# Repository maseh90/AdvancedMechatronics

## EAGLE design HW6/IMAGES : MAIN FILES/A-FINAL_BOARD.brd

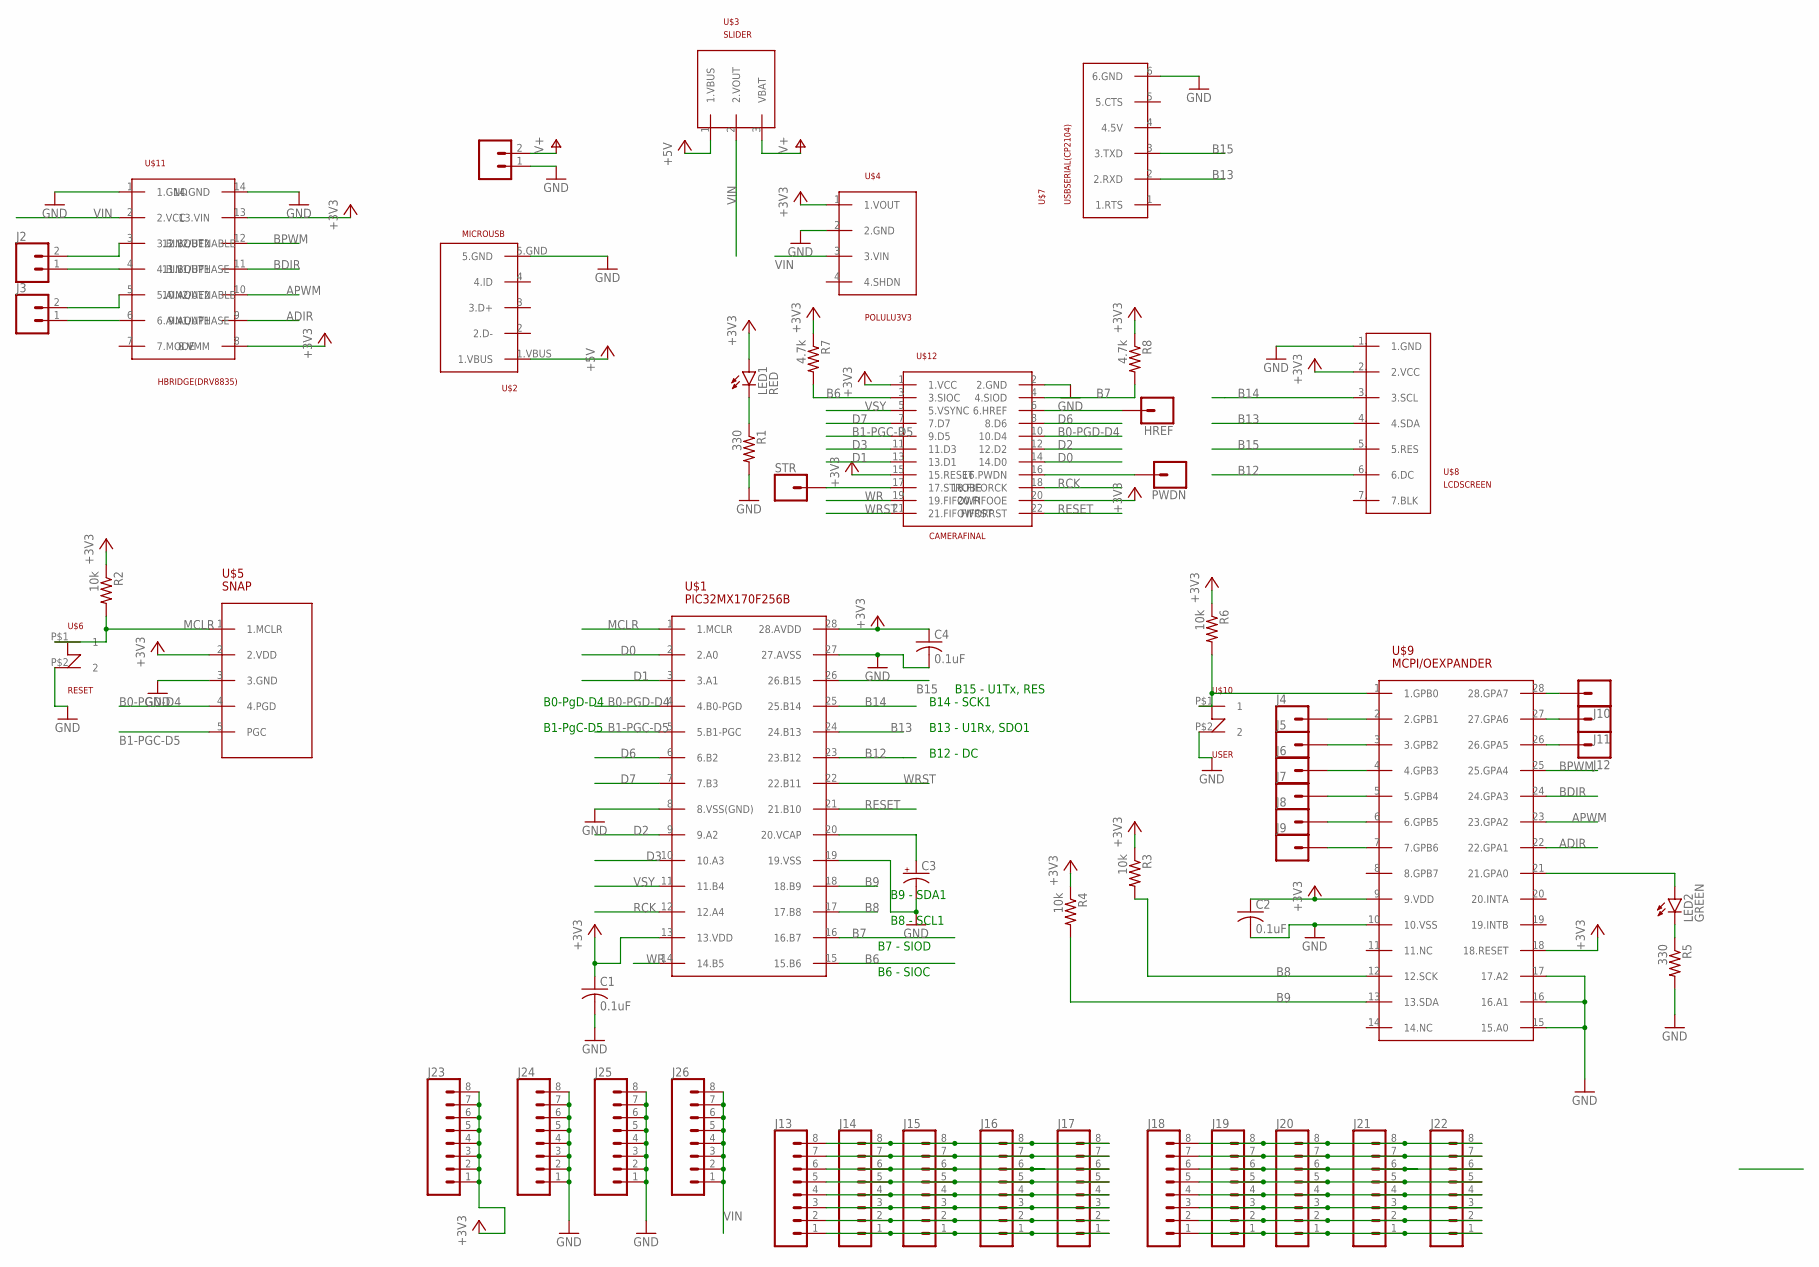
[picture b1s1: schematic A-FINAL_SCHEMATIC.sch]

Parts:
C1, C2, C4: 0.1uF; C025-030X050
C3: CPOL-USB45181B; B45181B
HREF: CONN_01; 1X01
J1: CONN_02-JST-2-PTH-NO_SILK; JST-2-PTH-NS
J2, J3: CONN_02; 1X02
J4, J5, J6, J7, J8, J9, J10, J11, J12: CONN_01; 1X01
J13, J14, J15, J16, J17, J18, J19, J20, J21, J22, J23, J24, J25, J26: CONN_08"; 1X08
LED1: RED; LED3MM
LED2: GREEN; LED3MM
PWDN: CONN_01; 1X01
R1, R5: 330; 0207/10
R2, R3, R4, R6: 10k; 0207/10
R7, R8: 4.7k; 0207/10
STR: CONN_01; 1X01
U$1: PIC32MX170F256B; DIL28-3
U$2: MICROUSB
U$3: SLIDER; SLIDE
U$4: POLULU3V3
U$5: SNAP; 1X05
U$6: RESET; PUSH
U$7: USBSERIAL(CP2104)
U$8: LCDSCREEN
U$9: MCPI/OEXPANDER
U$10: USER; PUSH
U$11: HBRIDGE(DRV8835)
U$12: CAMERAFINAL; CAMERA_FINAL

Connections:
+3V3: C1.1, C2.1, C4.1, J23.1, J23.2, J23.3, J23.4, J23.5, J23.6, J23.7, J23.8, LED1.A, R2.1, R3.1, R4.1, R6.1, R7.1, R8.1, U$1.13 (13.VDD), U$1.28 (28.AVDD), U$4.1 (1.VOUT), U$5.2 (2.VDD), U$8.2. (2.VCC), U$9.9 (9.VDD), U$9.18 (18.RESET), U$11.8 (8.VMM), U$11.13 (13.VIN), U$12.1 (1.VCC), U$12.15 (15.RESET), U$12.20 (20.FIFOOE)
+5V: U$2.1.VBUS, U$3.1 (1.VBUS)
ADIR: U$9.22 (22.GPA1), U$11.9 (9.AOUT1)
APWM: U$9.23 (23.GPA2), U$11.10 (10.AOUT2)
B0-PGD-D4: U$1.4 (4.B0-PGD), U$5.4 (4.PGD), U$12.10 (10.D4)
B1-PGC-D5: U$1.5 (5.B1-PGC), U$5.5 (PGC), U$12.9 (9.D5)
B6: R7.2, U$1.15 (15.B6), U$12.3 (3.SIOC)
B7: R8.2, U$1.16 (16.B7), U$12.4 (4.SIOD)
B8: R3.2, U$1.17 (17.B8), U$9.12 (12.SCK)
B9: R4.2, U$1.18 (18.B9), U$9.13 (13.SDA)
B12: U$1.23 (23.B12), U$8.6. (6.DC)
B13: U$1.24 (24.B13), U$7.2 (2.RXD), U$8.4. (4.SDA)
B14: U$1.25 (25.B14), U$8.3. (3.SCL)
B15: U$1.26 (26.B15), U$7.3 (3.TXD), U$8.5. (5.RES)
BDIR: U$9.24 (24.GPA3), U$11.11 (11.BOUT1)
BPWM: U$9.25 (25.GPA4), U$11.12 (12.BOUT2)
D0: U$1.2 (2.A0), U$12.14 (14.D0)
D1: U$1.3 (3.A1), U$12.13 (13.D1)
D2: U$1.9 (9.A2), U$12.12 (12.D2)
D3: U$1.10 (10.A3), U$12.11 (11.D3)
D6: U$1.6 (6.B2), U$12.8 (8.D6)
D7: U$1.7 (7.B3), U$12.7 (7.D7)
GND: C1.2, C2.2, C3.-, C4.2, J1.1, J24.1, J24.2, J24.3, J24.4, J24.5, J24.6, J24.7, J24.8, J25.1, J25.2, J25.3, J25.4, J25.5, J25.6, J25.7, J25.8, R1.2, R5.2, U$1.8 (8.VSS(GND)), U$1.19 (19.VSS), U$1.27 (27.AVSS), U$2.5.GND, U$4.2 (2.GND), U$5.3 (3.GND), U$6.P$2 (2), U$7.6 (6.GND), U$8.1. (1.GND), U$9.10 (10.VSS), U$9.15 (15.A0), U$9.16 (16.A1), U$9.17 (17.A2), U$10.P$2 (2), U$11.1 (1.GND), U$11.14 (14.GND), U$12.2 (2.GND)
MCLR: R2.2, U$1.1 (1.MCLR), U$5.1 (1.MCLR), U$6.P$1 (1)
unnamed: LED1.K (C), R1.1
unnamed: LED2.A, U$9.21 (21.GPA0)
unnamed: C3.+, U$1.20 (20.VCAP)
unnamed: LED2.K (C), R5.1
unnamed: R6.2, U$9.1 (1.GPB0), U$10.P$1 (1)
unnamed: J2.2, U$11.3 (3.BIN2/BENABLE)
unnamed: J2.1, U$11.4 (4.BIN1/BPHASE)
unnamed: J3.2, U$11.5 (5.AIN2/AENABLE)
unnamed: J3.1, U$11.6 (6.AIN1/APHASE)
unnamed: HREF.1, U$12.6 (6.HREF)
unnamed: PWDN.1, U$12.16 (16.PWDN)
unnamed: STR.1, U$12.17 (17.STROBE)
unnamed: J4.1, U$9.2 (2.GPB1)
unnamed: J5.1, U$9.3 (3.GPB2)
unnamed: J6.1, U$9.4 (4.GPB3)
unnamed: J7.1, U$9.5 (5.GPB4)
unnamed: J8.1, U$9.6 (6.GPB5)
unnamed: J9.1, U$9.7 (7.GPB6)
unnamed: J10.1, U$9.28 (28.GPA7)
unnamed: J11.1, U$9.27 (27.GPA6)
unnamed: J12.1, U$9.26 (26.GPA5)
unnamed: J18.8, J19.8, J20.8, J21.8, J22.8
unnamed: J13.8, J14.8, J15.8, J16.8, J17.8
unnamed: J18.7, J19.7, J20.7, J21.7, J22.7
unnamed: J18.6, J19.6, J20.6, J21.6, J22.6
unnamed: J18.5, J19.5, J20.5, J21.5, J22.5
unnamed: J18.4, J19.4, J20.4, J21.4, J22.4
unnamed: J18.3, J19.3, J20.3, J21.3, J22.3
unnamed: J18.2, J19.2, J20.2, J21.2, J22.2
unnamed: J18.1, J19.1, J20.1, J21.1, J22.1
unnamed: J13.7, J14.7, J15.7, J16.7, J17.7
unnamed: J13.6, J14.6, J15.6, J16.6, J17.6
unnamed: J13.5, J14.5, J15.5, J16.5, J17.5
unnamed: J13.4, J14.4, J15.4, J16.4, J17.4
unnamed: J13.3, J14.3, J15.3, J16.3, J17.3
unnamed: J13.2, J14.2, J15.2, J16.2, J17.2
unnamed: J13.1, J14.1, J15.1, J16.1, J17.1
RCK: U$1.12 (12.A4), U$12.18 (18.FIFORCK)
RESET: U$1.21 (21.B10), U$12.22 (FIFORRST)
V+: J1.2, U$3.3 (VBAT)
VIN: J26.1, J26.2, J26.3, J26.4, J26.5, J26.6, J26.7, J26.8, U$3.2 (2.VOUT), U$4.3 (3.VIN), U$11.2 (2.VCC)
VSY: U$1.11 (11.B4), U$12.5 (5.VSYNC)
WR: U$1.14 (14.B5), U$12.19 (19.FIFOWR)
WRST: U$1.22 (22.B11), U$12.21 (21.FIFOWRST)

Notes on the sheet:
B15 - U1Tx, RES
B13 - U1Rx, SDO1
B14 - SCK1
B12 - DC
B9 - SDA1
B8 - SCL1
B7 - SIOD
B6 - SIOC
B0-PgD-D4
B1-PgC-D5

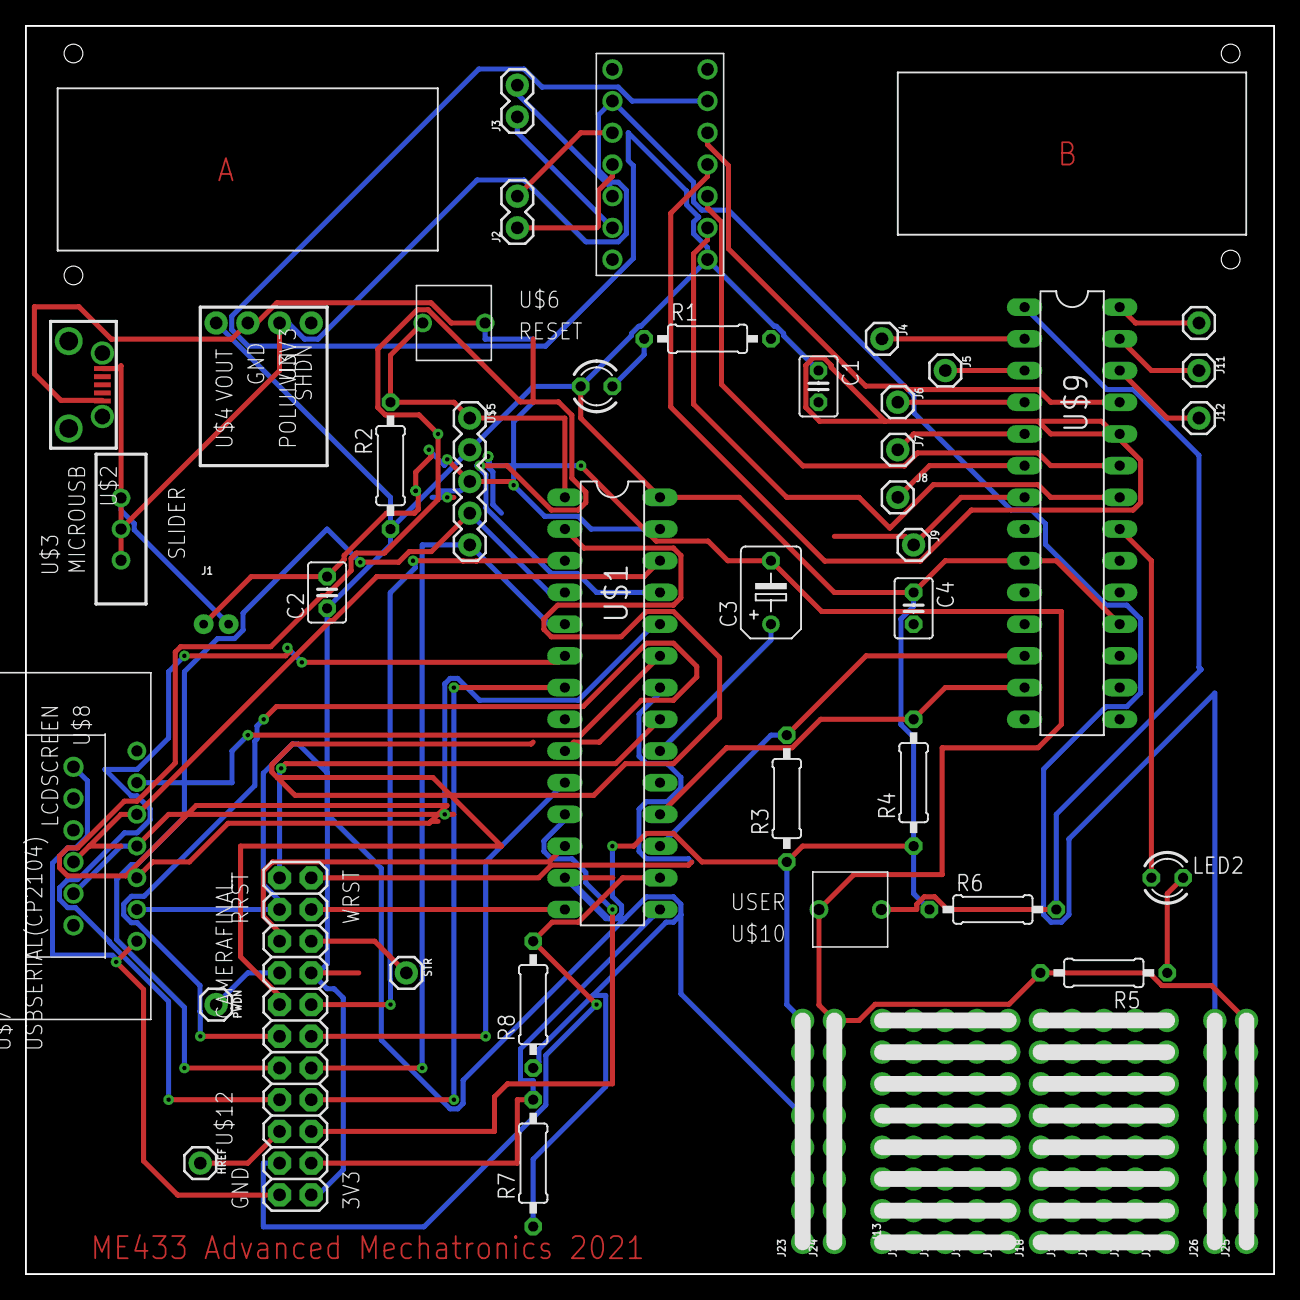
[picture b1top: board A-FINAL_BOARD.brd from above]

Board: 2 copper layers, 100.0 x 100.0 mm, 55 parts (0 on the bottom side), 68 nets.

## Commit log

2021-04-09 Uploaded HW2 Files
    This is my submission for HW2. I used a combination of the pre-provided reference code, the lecture video, online coding help guides (and StackOverflow), and documentation on choosing FIR filters. Th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
2021-04-17 Added HW3 (Lab Kit picture) folder
2021-04-18 Uploaded HW4 manually in browser
    I kept receiving "Unable to merge unrelated histories in this repository." errors, so I dragged/dropped the HW4 files here.
2021-04-18 Deleted HW4 directory
2021-04-18 Added HW4 files manually in browser
    I manually dragged/dropped the HW4 file here because I kept receiving "Unable to merge unrelated histories in this repository." messages after changing the original project name.
2021-04-18 Added Requested Images to HW4
2021-04-25 Added HW5 program files
2021-04-25 deleted for re-upload
2021-04-25 Added HW5 program files again
2021-05-03 Added HW7 screenshots and code
2021-05-03 Incorrect title. Will reupload
2021-05-03 Added final HW7 files with correct folder title
2021-05-04 Added HW6 submission
2021-05-06 Uploaded HW8 code
2021-05-08 Added HW9 files
2021-05-29 Added HW 10 files
2021-06-02 Uploaded HW11 files
2021-06-10 Added HW 14 files
2021-06-10 Deleted directory (incorrect name format)
2021-06-10 Re-uploaded HW14 files with correct folder name
